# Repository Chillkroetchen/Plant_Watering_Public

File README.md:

# Plant_Watering
For use:
    1. configure variables in userConfig_sample.h
    2. rename userConfig_sample.h to userConfig.h
    3. build and upload to ESP32

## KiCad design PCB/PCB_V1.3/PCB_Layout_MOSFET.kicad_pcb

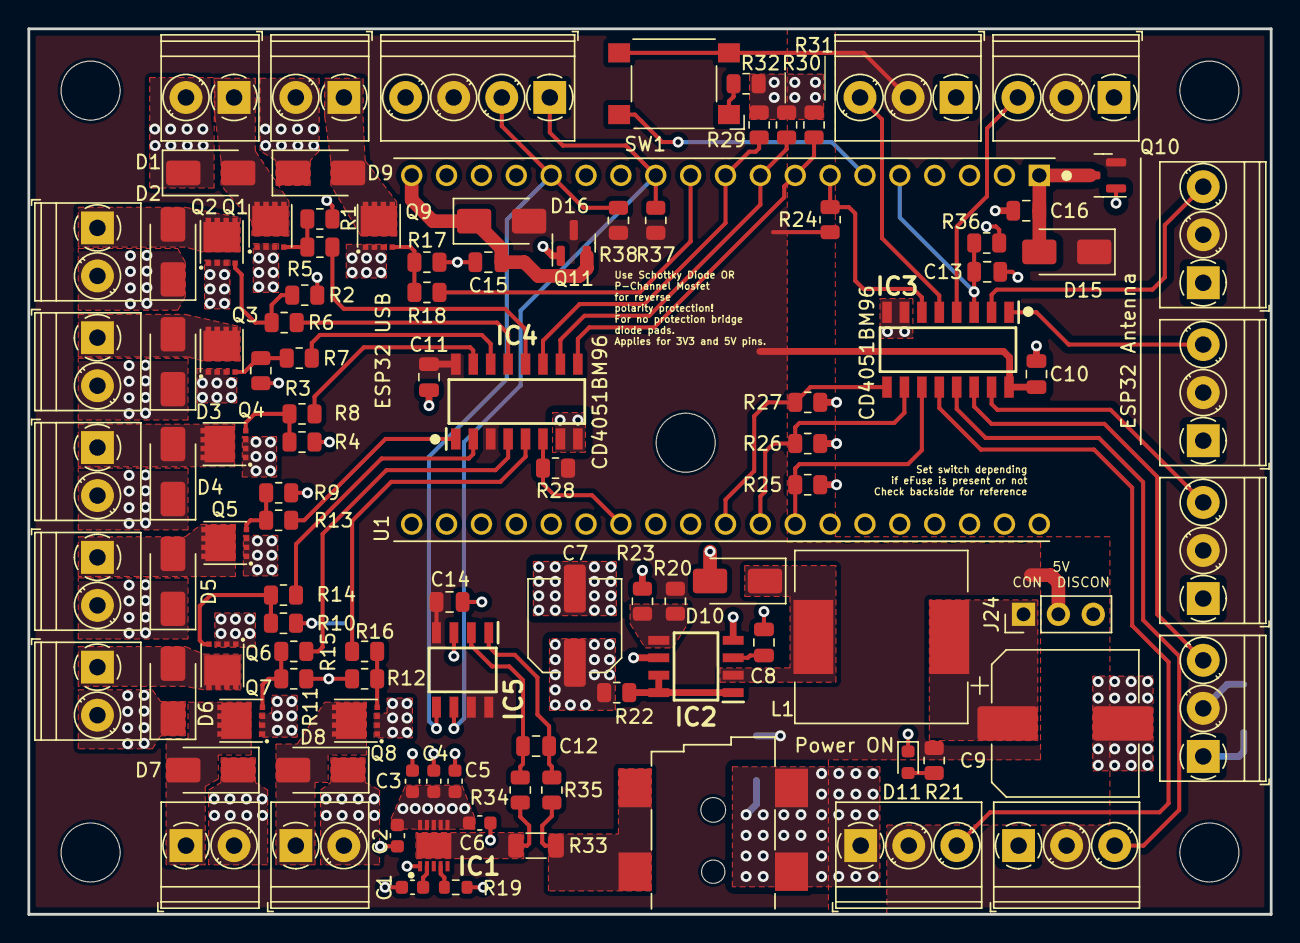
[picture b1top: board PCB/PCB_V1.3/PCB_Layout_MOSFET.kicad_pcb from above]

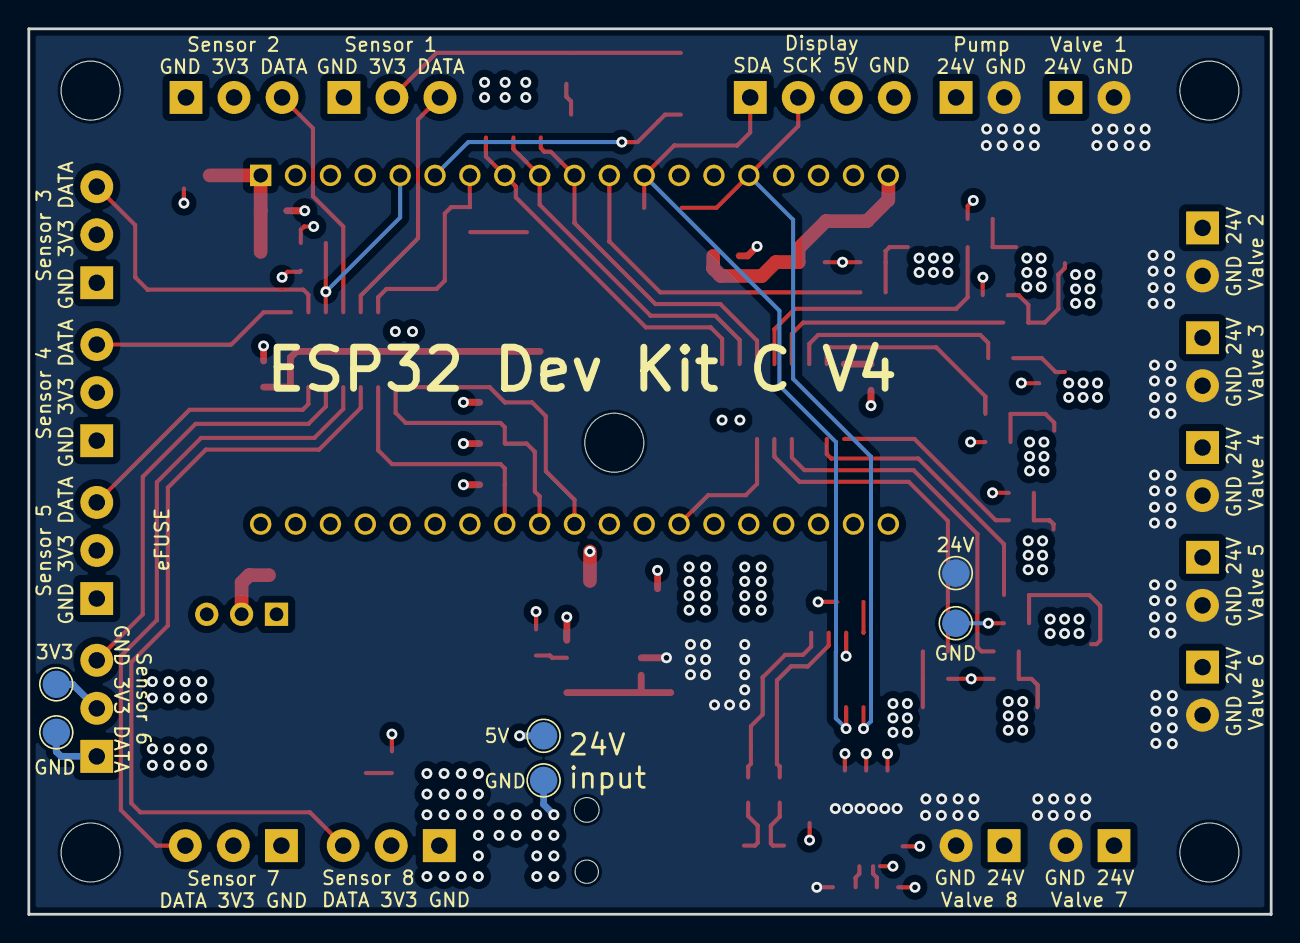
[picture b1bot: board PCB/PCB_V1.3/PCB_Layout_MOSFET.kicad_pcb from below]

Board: 4 copper layers, 90.5 x 64.5 mm, 117 parts (6 on the bottom side), 66 nets.

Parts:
C1: 470pF; C_0603_1608Metric
C2, C3, C4, C5, C6: 100nF; C_0603_1608Metric
C7: 100uF; CP_Elec_6.3x7.7
C8: 470pF; C_0805_2012Metric
C9: 470uF; CP_Elec_10x10.5
C10, C11, C12, C13, C14, C15, C16: 100nF; C_0805_2012Metric
D1, D2, D3, D4, D5, D6, D7, D8, D9, D10, D15, D16: 1N5819; D_SMA
D11: LED Blue; LED_0603_1608Metric
H1, H2, H3, H4, H5: MountingHole; MountingHole_4.3mm_M4
IC1: NIS4461MT3TXG; SON50P300X300X80-11N
IC2: MC34063ADR2G; SOIC127P600X175-8N
IC3, IC4: CD4051BM96; SOIC127P600X175-16N
IC5: INA219AIDR; SOIC127P600X175-8N
J1, J2, J3, J4, J5, J6, J7, J8, J9: Screw_Terminal_01x02; TerminalBlock_Phoenix_PT-1,5-2-3.5-H_1x02_P3.50mm_Horizontal
J10: KH-DC-050-2.0STM; CUI_PJ-002BH-SMT-TR
J11, J12, J13, J14, J15, J16, J17, J18: Screw_Terminal_01x03; TerminalBlock_Phoenix_PT-1,5-3-3.5-H_1x03_P3.50mm_Horizontal
J19: Screw_Terminal_01x04; TerminalBlock_Phoenix_PT-1,5-4-3.5-H_1x04_P3.50mm_Horizontal
J24: Conn_01x03; PinHeader_1x03_P2.54mm_Vertical
L1: 220uH; L_12x12mm_H8mm_3D
Q1, Q2, Q3, Q4, Q5, Q6, Q7, Q8, Q9: TPN2R805PL,L1Q; TPN2R805PLL1Q
Q10, Q11: SE3415; SOT-23
R1, R2, R3, R4, R9, R10, R11, R12, R17, R20, R37, R38: 3.6k; R_0805_2012Metric
R5, R6, R7, R8, R13, R14, R15, R16, R18: 330; R_0805_2012Metric
R19: 20; R_0603_1608Metric
R21, R23: 1.2k; R_0805_2012Metric
R22: 0.33; R_0805_2012Metric
R24, R25, R26, R27, R28, R29, R30, R31, R32, R36: 1M; R_0805_2012Metric
R33: R_Shunt_20m; R_1206_3216Metric
R34, R35: 0; R_0805_2012Metric
SW1: SW_MEC_5E; SW_SPST_Omron_B3FS-100xP_3D
TP1, TP2, TP3, TP4, TP5, TP6: TestPoint; TestPoint_Pad_D2.0mm
U1: ESP32-DEVKITC-32D; MODULE_ESP32-DEVKITC-32D

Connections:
3V3: D15.1 (K), J11.2, J12.2, J13.2, J14.2, J15.2, J16.2, J17.2, J18.2, Q10.2 (S), SW1.3 (K), SW1.4 (A), TP4.1
5V: C10.1, C11.1, C14.1, D16.2 (A), IC3.16 (VDD), IC4.3 (Z), IC4.16 (VDD), IC5.4 (VS), IC5.7 (A0), IC5.8 (A1), J19.3, J24.2, Q11.3 (D), R20.2, R21.2, R24.1, R28.1, R37.1, R38.1, TP1.1
5V_raw: C9.1, J24.1, L1.1
24V: C2.1, C3.1, C4.1, C5.1, C6.1, C7.1, D1.1 (K), D2.1 (K), D3.1 (K), D4.1 (K), D5.1 (K), D6.1 (K), D7.1 (K), D8.1 (K), D9.1 (K), IC1.6 (SRC_1), IC1.7 (SRC_2), IC1.8 (SRC_3), IC1.9 (SRC_4), IC1.10 (SRC_5), IC2.6 (VCC), J1.2, J2.2, J3.2, J4.2, J5.2, J6.2, J7.2, J8.2, J9.2, R19.1, R22.1, TP3.1
24V_raw: J10.1A, J10.1B, R33.1, R33.2, R35.2
24V_sensed: IC1.11 (EP), R33.3, R33.4, R34.2
/EXT_3V3: C16.1, D15.2 (A), Q10.3 (D), U1.1 (3V3)
/EXT_5V: C15.1, D16.1 (K), Q11.2 (S), U1.19 (EXT_5V)
/High Power Externals/Q1_drain: D1.2 (A), J1.1, Q1.5 (D_1), Q1.6 (D_2), Q1.7 (D_3), Q1.8 (D_4), Q1.9 (D_5)
/High Power Externals/Q1_gate: Q1.4 (G), R1.1, R5.1
/High Power Externals/Q2_drain: D2.2 (A), J2.1, Q2.5 (D_1), Q2.6 (D_2), Q2.7 (D_3), Q2.8 (D_4), Q2.9 (D_5)
/High Power Externals/Q2_gate: Q2.4 (G), R2.1, R6.1
/High Power Externals/Q3_drain: D3.2 (A), J3.1, Q3.5 (D_1), Q3.6 (D_2), Q3.7 (D_3), Q3.8 (D_4), Q3.9 (D_5)
/High Power Externals/Q3_gate: Q3.4 (G), R3.1, R7.1
/High Power Externals/Q4_drain: D4.2 (A), J4.1, Q4.5 (D_1), Q4.6 (D_2), Q4.7 (D_3), Q4.8 (D_4), Q4.9 (D_5)
/High Power Externals/Q4_gate: Q4.4 (G), R4.1, R8.1
/High Power Externals/Q5_drain: D5.2 (A), J5.1, Q5.5 (D_1), Q5.6 (D_2), Q5.7 (D_3), Q5.8 (D_4), Q5.9 (D_5)
/High Power Externals/Q5_gate: Q5.4 (G), R9.1, R13.1
/High Power Externals/Q6_drain: D6.2 (A), J6.1, Q6.5 (D_1), Q6.6 (D_2), Q6.7 (D_3), Q6.8 (D_4), Q6.9 (D_5)
/High Power Externals/Q6_gate: Q6.4 (G), R10.1, R14.1
/High Power Externals/Q7_drain: D7.2 (A), J7.1, Q7.5 (D_1), Q7.6 (D_2), Q7.7 (D_3), Q7.8 (D_4), Q7.9 (D_5)
/High Power Externals/Q7_gate: Q7.4 (G), R11.1, R15.1
/High Power Externals/Q8_drain: D8.2 (A), J8.1, Q8.5 (D_1), Q8.6 (D_2), Q8.7 (D_3), Q8.8 (D_4), Q8.9 (D_5)
/High Power Externals/Q8_gate: Q8.4 (G), R12.1, R16.1
/High Power Externals/Q9_drain: D9.2 (A), J9.1, Q9.5 (D_1), Q9.6 (D_2), Q9.7 (D_3), Q9.8 (D_4), Q9.9 (D_5)
/High Power Externals/Q9_gate: Q9.4 (G), R17.1, R18.1
/Power Supply/CII: IC2.5 (CII), R20.1, R23.2
/Power Supply/I Lim: IC1.4 (ILIM), R19.2
/Power Supply/LED: D11.2 (A), R21.1
/Power Supply/SWC: IC2.1 (SWC), IC2.7 (IPK), IC2.8 (DRC), R22.2
/Power Supply/SWE: D10.1 (K), IC2.2 (SWE), L1.2
/Power Supply/TC: C8.1, IC2.3 (TC)
/Power Supply/dV/dT: C1.1, IC1.2 (DV/DT)
Button: SW1.2, U1.6 (IO35)
GND: C1.2, C2.2, C3.2, C4.2, C5.2, C6.2, C7.2, C8.2, C9.2, C10.2, C11.2, C13.2, C14.2, C15.2, C16.2, D10.2 (A), D11.1 (K), IC1.1 (GND), IC2.4 (GND), IC3.7 (VEE), IC3.8 (VSS), IC4.7 (VEE), IC4.8 (VSS), IC5.3 (GND), J10.2, J10.3, J11.1, J12.1, J13.1, J14.1, J15.1, J16.1, J17.1, J18.1, J19.4, Q1.1 (S_1), Q1.2 (S_2), Q1.3 (S_3), Q2.1 (S_1), Q2.2 (S_2), Q2.3 (S_3), Q3.1 (S_1), Q3.2 (S_2), Q3.3 (S_3), Q4.1 (S_1), Q4.2 (S_2), Q4.3 (S_3), Q5.1 (S_1), Q5.2 (S_2), Q5.3 (S_3), Q6.1 (S_1), Q6.2 (S_2), Q6.3 (S_3), Q7.1 (S_1), Q7.2 (S_2), Q7.3 (S_3), Q8.1 (S_1), Q8.2 (S_2), Q8.3 (S_3), Q9.1 (S_1), Q9.2 (S_2), Q9.3 (S_3), Q10.1 (G), Q11.1 (G), R1.2, R2.2, R3.2, R4.2, R9.2, R10.2, R11.2, R12.2, R17.2, R23.1, R25.1, R26.1, R27.1, R29.1, R30.1, R31.1, R32.2, R36.1, TP2.1, TP5.1, TP6.1, U1.14 (GND1), U1.20 (GND3), U1.26 (GND2)
unnamed: C12.1, IC5.1 (IN+), R35.1
unnamed: C12.2, IC5.2 (IN-), R34.1
unnamed: R32.1, SW1.1
Pump_Gate: R18.2, U1.11 (IO27)
SCL: IC5.5 (SCL), J19.2, R38.2, U1.15 (IO13)
SDA: IC5.6 (SDA), J19.1, R37.2, U1.12 (IO14)
Sensors_Enable: IC3.6 (~E), R24.2, U1.7 (IO32)
Sensors_Select1: IC3.11 (S1), R25.2, U1.27 (IO19)
Sensors_Select2: IC3.10 (S2), R26.2, U1.28 (IO18)
Sensors_Select3: IC3.9 (S3), R27.2, U1.29 (IO5)
Sensors_Signal: C13.1, IC3.3 (Z), R36.2, U1.5 (IO34)
Valves_Enable: IC4.6 (~E), R28.2, U1.32 (IO4)
Valves_Select1: IC4.11 (S1), R29.2, U1.10 (IO26)
Valves_Select2: IC4.10 (S2), R30.2, U1.9 (IO25)
Valves_Select3: IC4.9 (S3), R31.2, U1.8 (IO33)
Y0: IC4.13 (Y0), R6.2
Y0.2: IC3.13 (Y0), J17.3
Y1: IC4.14 (Y1), R7.2
Y1.2: IC3.14 (Y1), J16.3
Y2: IC4.15 (Y2), R8.2
Y2.2: IC3.15 (Y2), J15.3
Y3: IC4.12 (Y3), R5.2
Y3.2: IC3.12 (Y3), J18.3
Y4: IC4.1 (Y4), R13.2
Y4.2: IC3.1 (Y4), J14.3
Y5: IC4.5 (Y5), R16.2
Y5.2: IC3.5 (Y5), J11.3
Y6: IC4.2 (Y6), R14.2
Y6.2: IC3.2 (Y6), J13.3
Y7: IC4.4 (Y7), R15.2
Y7.2: IC3.4 (Y7), J12.3

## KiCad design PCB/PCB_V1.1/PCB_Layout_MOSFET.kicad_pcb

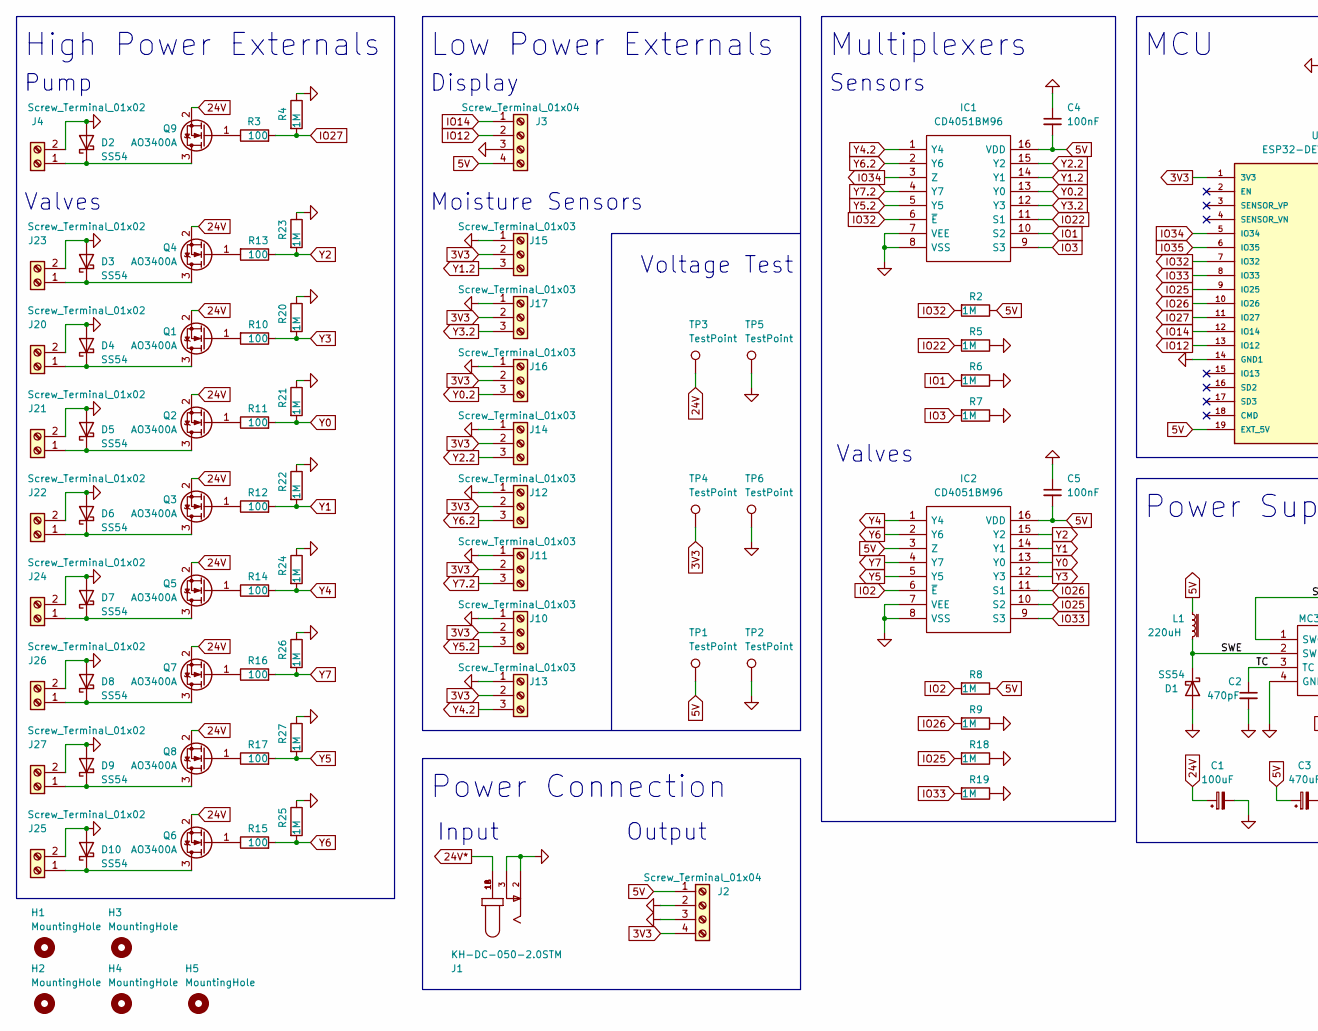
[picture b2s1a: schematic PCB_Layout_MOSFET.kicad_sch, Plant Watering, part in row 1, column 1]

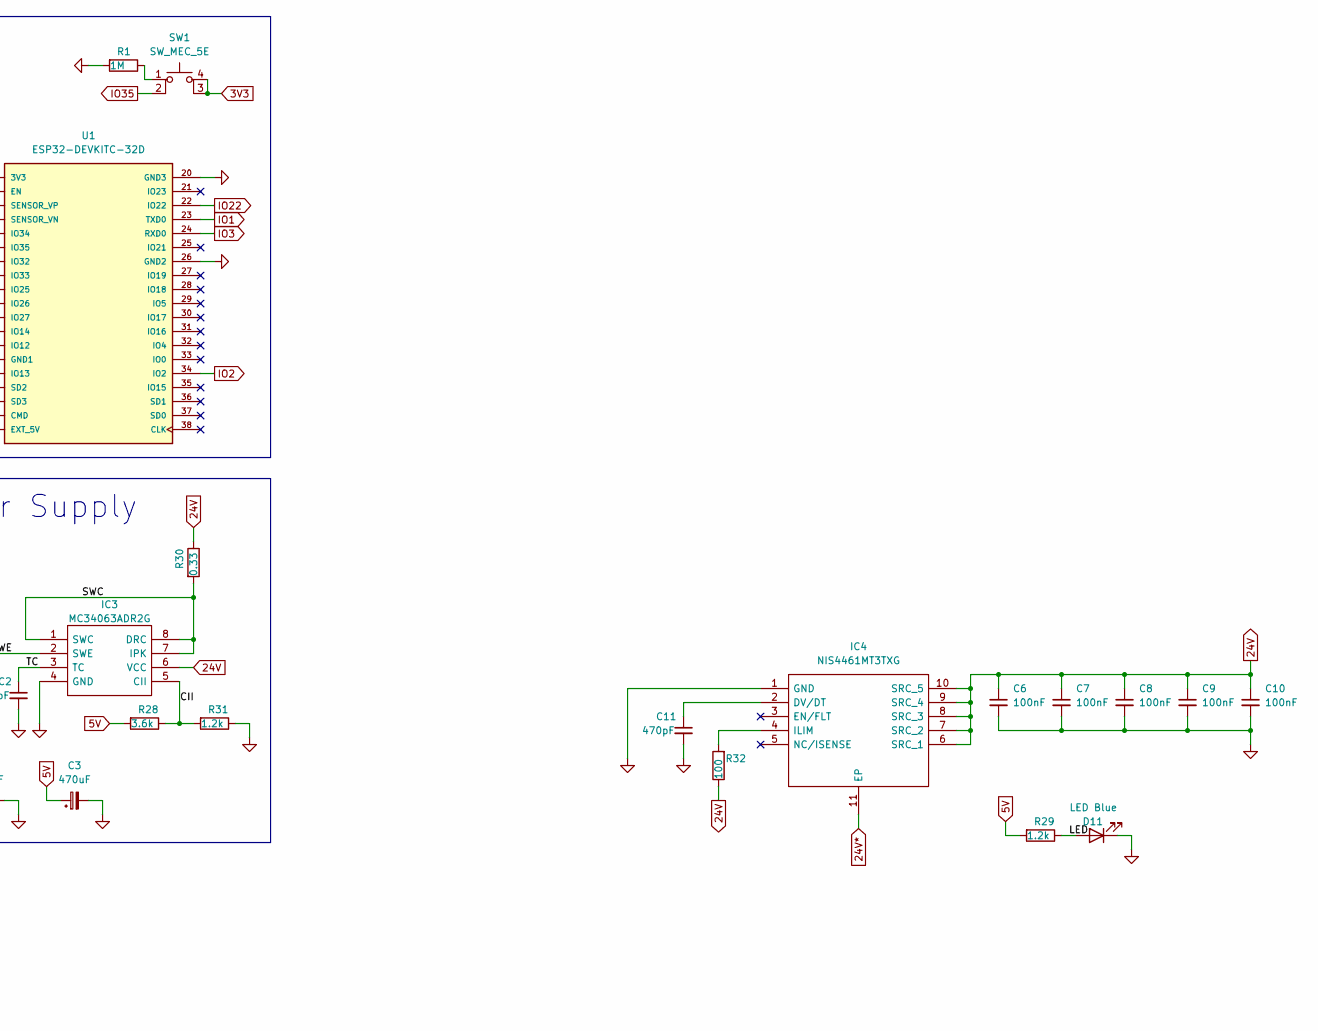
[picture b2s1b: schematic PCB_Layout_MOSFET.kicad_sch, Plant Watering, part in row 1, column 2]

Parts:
C1: 100uF; CP_Elec_6.3x7.7; LCSC C3001220
C2: 470pF; C_0805_2012Metric; LCSC C1743
C3: 470uF; CP_Elec_10x10.5; LCSC C129479
C4, C5: 100nF; C_0805_2012Metric; LCSC C49678
C6, C7, C8, C9, C10: 100nF; C_0603_1608Metric; LCSC C14663
C11: 470pF; C_0603_1608Metric; LCSC C1620
D1, D2, D3, D4, D5, D6, D7, D8, D9, D10: SS54; D_SMA; LCSC C22452
D11: LED Blue; LED_0603_1608Metric; LCSC C72041
H1, H2, H3, H4, H5: MountingHole; MountingHole_4.3mm_M4
IC1, IC2: CD4051BM96; SOIC127P600X175-16N; Manufacturer_Part_Number CD4051BM96; LCSC C21379
IC3: MC34063ADR2G; SOIC127P600X175-8N; LCSC C32078
IC4: NIS4461MT3TXG; SON50P300X300X80-11N; Mouser Part Number 863-NIS4461MT3TXG
J1: KH-DC-050-2.0STM; CUI_PJ-002BH-SMT-TR; LCSC C2847201
J2, J3: Screw_Terminal_01x04; TerminalBlock_Phoenix_PT-1,5-4-3.5-H_1x04_P3.50mm_Horizontal; LCSC C2757925
J4, J20, J21, J22, J23, J24, J25, J26, J27: Screw_Terminal_01x02; TerminalBlock_Phoenix_PT-1,5-2-3.5-H_1x02_P3.50mm_Horizontal; LCSC C474930
J10, J11, J12, J13, J14, J15, J16, J17: Screw_Terminal_01x03; TerminalBlock_Phoenix_PT-1,5-3-3.5-H_1x03_P3.50mm_Horizontal; LCSC C474931
L1: 220uH; L_1210_3225Metric; LCSC C394104
Q1, Q2, Q3, Q4, Q5, Q6, Q7, Q8, Q9: AO3400A; SOT-23; LCSC C20917
R1, R2, R4, R5, R6, R7, R8, R9, R18, R19, R20, R21, R22, R23, R24, R25, R26, R27: 1M; R_0805_2012Metric; LCSC C17514
R3, R10, R11, R12, R13, R14, R15, R16, R17: 100; R_0805_2012Metric; LCSC C17408
R28: 3.6k; R_0805_2012Metric; LCSC C18359
R29, R31: 1.2k; R_0805_2012Metric; LCSC C17379
R30: 0.33; R_0805_2012Metric; LCSC C491232
R32: 100; R_0603_1608Metric; LCSC C22775
SW1: SW_MEC_5E; SW_SPST_Omron_B3FS-100xP_3D; LCSC C231324
TP1, TP2, TP3, TP4, TP5, TP6: TestPoint; TestPoint_Pad_D2.0mm
U1: ESP32-DEVKITC-32D; MODULE_ESP32-DEVKITC-32D; PARTREV 4

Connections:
3V3: J2.4, J10.2, J11.2, J12.2, J13.2, J14.2, J15.2, J16.2, J17.2, SW1.3 (K), SW1.4 (A), TP4.1, U1.1 (3V3)
5V: C3.1, C4.2, C5.2, IC1.16 (VDD), IC2.3 (Z), IC2.16 (VDD), J2.1, J3.4, L1.1, R2.1, R8.1, R28.2, R29.2, TP1.1, U1.19 (EXT_5V)
24V: C1.1, C6.1, C7.1, C8.1, C9.1, C10.1, IC3.6 (VCC), IC4.6 (SRC_1), IC4.7 (SRC_2), IC4.8 (SRC_3), IC4.9 (SRC_4), IC4.10 (SRC_5), Q1.2 (S), Q2.2 (S), Q3.2 (S), Q4.2 (S), Q5.2 (S), Q6.2 (S), Q7.2 (S), Q8.2 (S), Q9.2 (S), R30.1, R32.1, TP3.1
24V*: IC4.11 (EP), J1.1A, J1.1B
/CII: IC3.5 (CII), R28.1, R31.2
/LED: D11.2 (A), R29.1
/SWC: IC3.1 (SWC), IC3.7 (IPK), IC3.8 (DRC), R30.2
/SWE: D1.1 (K), IC3.2 (SWE), L1.2
/TC: C2.1, IC3.3 (TC)
GND: C1.2, C2.2, C3.2, C4.1, C5.1, C6.2, C7.2, C8.2, C9.2, C10.2, C11.2, D1.2 (A), D2.2 (A), D3.2 (A), D4.2 (A), D5.2 (A), D6.2 (A), D7.2 (A), D8.2 (A), D9.2 (A), D10.2 (A), D11.1 (K), IC1.7 (VEE), IC1.8 (VSS), IC2.7 (VEE), IC2.8 (VSS), IC3.4 (GND), IC4.1 (GND), J1.2, J1.3, J2.2, J2.3, J3.3, J4.2, J10.1, J11.1, J12.1, J13.1, J14.1, J15.1, J16.1, J17.1, J20.2, J21.2, J22.2, J23.2, J24.2, J25.2, J26.2, J27.2, R1.2, R4.1, R5.1, R6.1, R7.1, R9.1, R18.1, R19.1, R20.1, R21.1, R22.1, R23.1, R24.1, R25.1, R26.1, R27.1, R31.1, TP2.1, TP5.1, TP6.1, U1.14 (GND1), U1.20 (GND3), U1.26 (GND2)
IO1: IC1.10 (S2), R6.2, U1.23 (TXD0)
IO2: IC2.6 (~E), R8.2, U1.34 (IO2)
IO3: IC1.9 (S3), R7.2, U1.24 (RXD0)
IO12: J3.2, U1.13 (IO12)
IO14: J3.1, U1.12 (IO14)
IO22: IC1.11 (S1), R5.2, U1.22 (IO22)
IO25: IC2.10 (S2), R18.2, U1.9 (IO25)
IO26: IC2.11 (S1), R9.2, U1.10 (IO26)
IO27: R3.2, R4.2, U1.11 (IO27)
IO32: IC1.6 (~E), R2.2, U1.7 (IO32)
IO33: IC2.9 (S3), R19.2, U1.8 (IO33)
IO34: IC1.3 (Z), U1.5 (IO34)
IO35: SW1.2, U1.6 (IO35)
unnamed: C11.1, IC4.2 (DV/DT)
unnamed: D2.1 (K), J4.1, Q9.3 (D)
unnamed: D3.1 (K), J23.1, Q4.3 (D)
unnamed: D4.1 (K), J20.1, Q1.3 (D)
unnamed: D5.1 (K), J21.1, Q2.3 (D)
unnamed: D6.1 (K), J22.1, Q3.3 (D)
unnamed: D7.1 (K), J24.1, Q5.3 (D)
unnamed: D8.1 (K), J26.1, Q7.3 (D)
unnamed: D9.1 (K), J27.1, Q8.3 (D)
unnamed: D10.1 (K), J25.1, Q6.3 (D)
unnamed: IC4.4 (ILIM), R32.2
unnamed: Q1.1 (G), R10.2
unnamed: Q2.1 (G), R11.1
unnamed: Q3.1 (G), R12.1
unnamed: Q4.1 (G), R13.2
unnamed: Q5.1 (G), R14.1
unnamed: Q6.1 (G), R15.1
unnamed: Q7.1 (G), R16.1
unnamed: Q8.1 (G), R17.1
unnamed: Q9.1 (G), R3.1
unnamed: R1.1, SW1.1
Y0: IC2.13 (Y0), R11.2, R21.2
Y0.2: IC1.13 (Y0), J16.3
Y1: IC2.14 (Y1), R12.2, R22.2
Y1.2: IC1.14 (Y1), J15.3
Y2: IC2.15 (Y2), R13.1, R23.2
Y2.2: IC1.15 (Y2), J14.3
Y3: IC2.12 (Y3), R10.1, R20.2
Y3.2: IC1.12 (Y3), J17.3
Y4: IC2.1 (Y4), R14.2, R24.2
Y4.2: IC1.1 (Y4), J13.3
Y5: IC2.5 (Y5), R17.2, R27.2
Y5.2: IC1.5 (Y5), J10.3
Y6: IC2.2 (Y6), R15.2, R25.2
Y6.2: IC1.2 (Y6), J12.3
Y7: IC2.4 (Y7), R16.2, R26.2
Y7.2: IC1.4 (Y7), J11.3

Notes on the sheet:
Power Supply
Valves
Multiplexers
Pump
Input
Moisture Sensors
Sensors
Power Connection
Output
Low Power Externals
Voltage Test
MCU
High Power Externals
Display

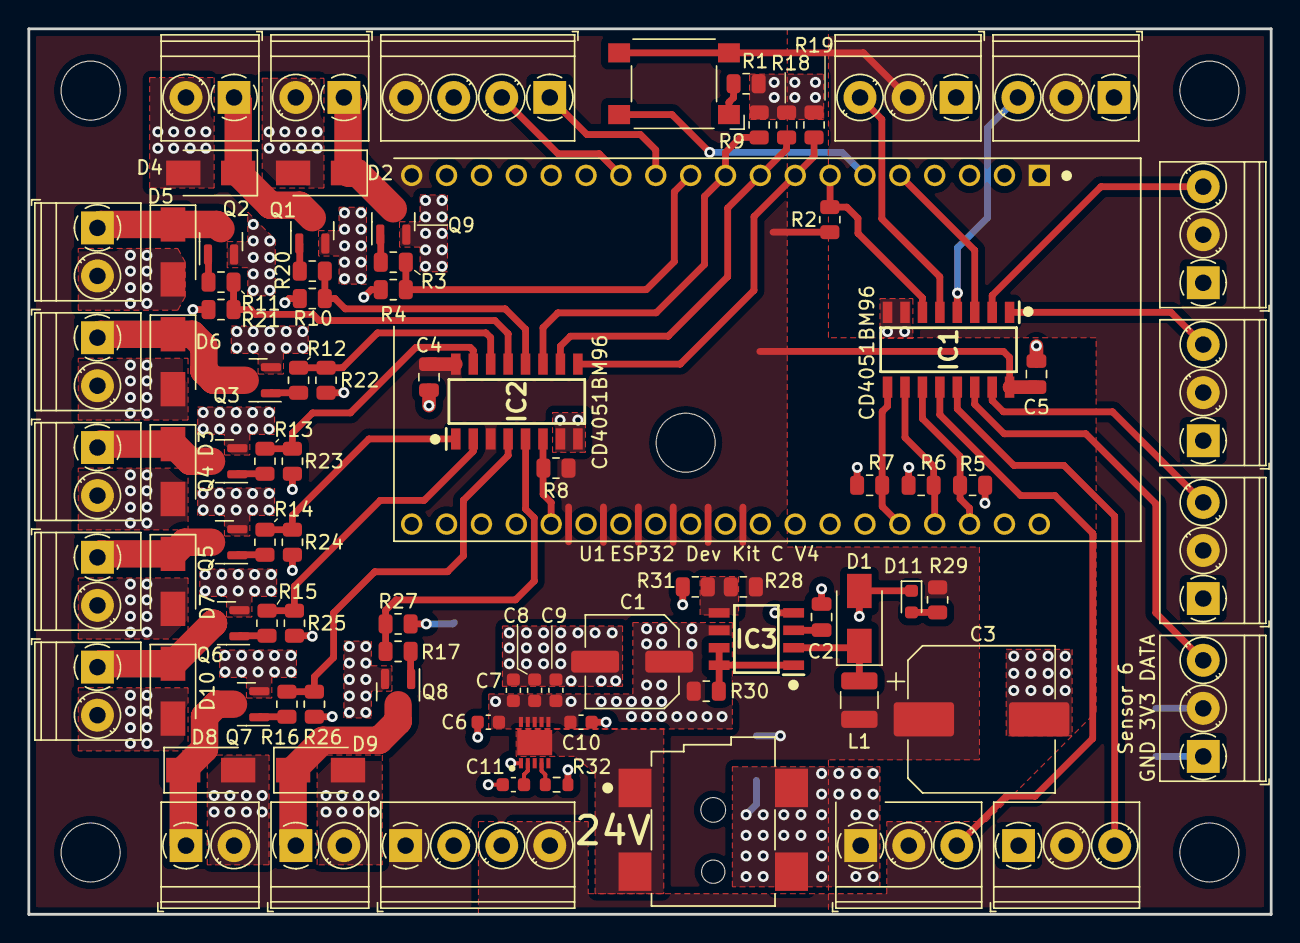
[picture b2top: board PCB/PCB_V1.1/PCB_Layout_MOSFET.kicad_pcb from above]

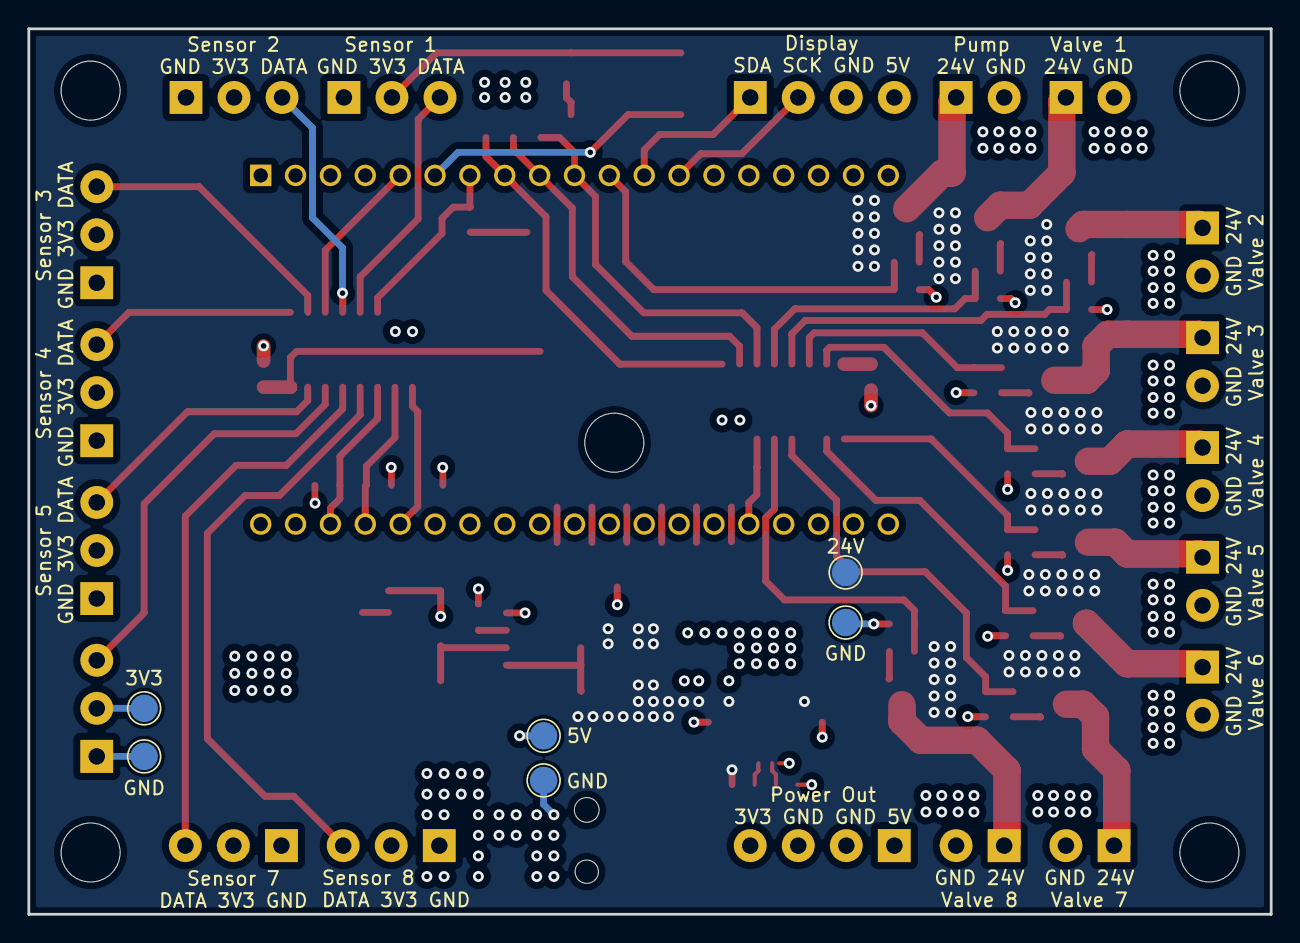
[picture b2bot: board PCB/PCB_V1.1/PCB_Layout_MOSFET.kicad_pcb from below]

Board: 4 copper layers, 90.5 x 64.5 mm, 101 parts (6 on the bottom side), 60 nets.

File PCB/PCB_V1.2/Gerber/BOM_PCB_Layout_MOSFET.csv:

Comment,Designator,Footprint,LCSC
"470pF","C1","Capacitor_SMD:C_0805_2012Metric","C1743"
"470uF","C2","Capacitor_SMD:CP_Elec_10x10.5","C129479"
"100uF","C3","Capacitor_SMD:CP_Elec_6.3x7.7","C3001220"
"LED Blue","D1","LED_SMD:LED_0603_1608Metric","C72041"
"SS54","D2,D3,D4,D5,D6,D7,D8,D9,D10,D11","Diode_SMD:D_SMA","C22452"
"HEF4051BT,653","IC1,IC2","SamacSys_Parts:SOIC127P600X175-16N","C11351"
"MC34063ADR2G","IC3","SamacSys_Parts:SOIC127P600X175-8N","C32078"
"KH-DC-050-2.0STM","J1","PersonalLibrary:CUI_PJ-002BH-SMT-TR","C2847201"
"Screw_Terminal_01x03","J10,J11,J12,J13,J14,J15,J16,J17","TerminalBlock_Phoenix:TerminalBlock_Phoenix_PT-1,5-3-3.5-H_1x03_P3.50mm_Horizontal","C474931"
"Screw_Terminal_01x04","J2,J3","TerminalBlock_Phoenix:TerminalBlock_Phoenix_PT-1,5-4-3.5-H_1x04_P3.50mm_Horizontal","C2757925"
"Screw_Terminal_01x02","J4,J20,J21,J22,J23,J24,J25,J26,J27","TerminalBlock_Phoenix:TerminalBlock_Phoenix_PT-1,5-2-3.5-H_1x02_P3.50mm_Horizontal","C474930"
"220uH","L1","Inductor_SMD:L_1210_3225Metric","C394104"
"AO3400A","Q1,Q2,Q3,Q4,Q5,Q6,Q7,Q8,Q9","Package_TO_SOT_SMD:SOT-23","C20917"
"1M","R1,R4,R20,R21,R22,R23,R24,R25,R26,R27","Resistor_SMD:R_0805_2012Metric","C17514"
"100","R2,R3,R10,R11,R12,R13,R14,R15,R16,R17","Resistor_SMD:R_0805_2012Metric","C17408"
"3.6k","R5","Resistor_SMD:R_0805_2012Metric","C18359"
"0.33","R6","Resistor_SMD:R_0805_2012Metric","C491232"
"1.2k","R7","Resistor_SMD:R_0805_2012Metric","C17379"
"SW_MEC_5E","SW1","PersonalLibrary:SW_SPST_Omron_B3FS-100xP_3D","C231324"

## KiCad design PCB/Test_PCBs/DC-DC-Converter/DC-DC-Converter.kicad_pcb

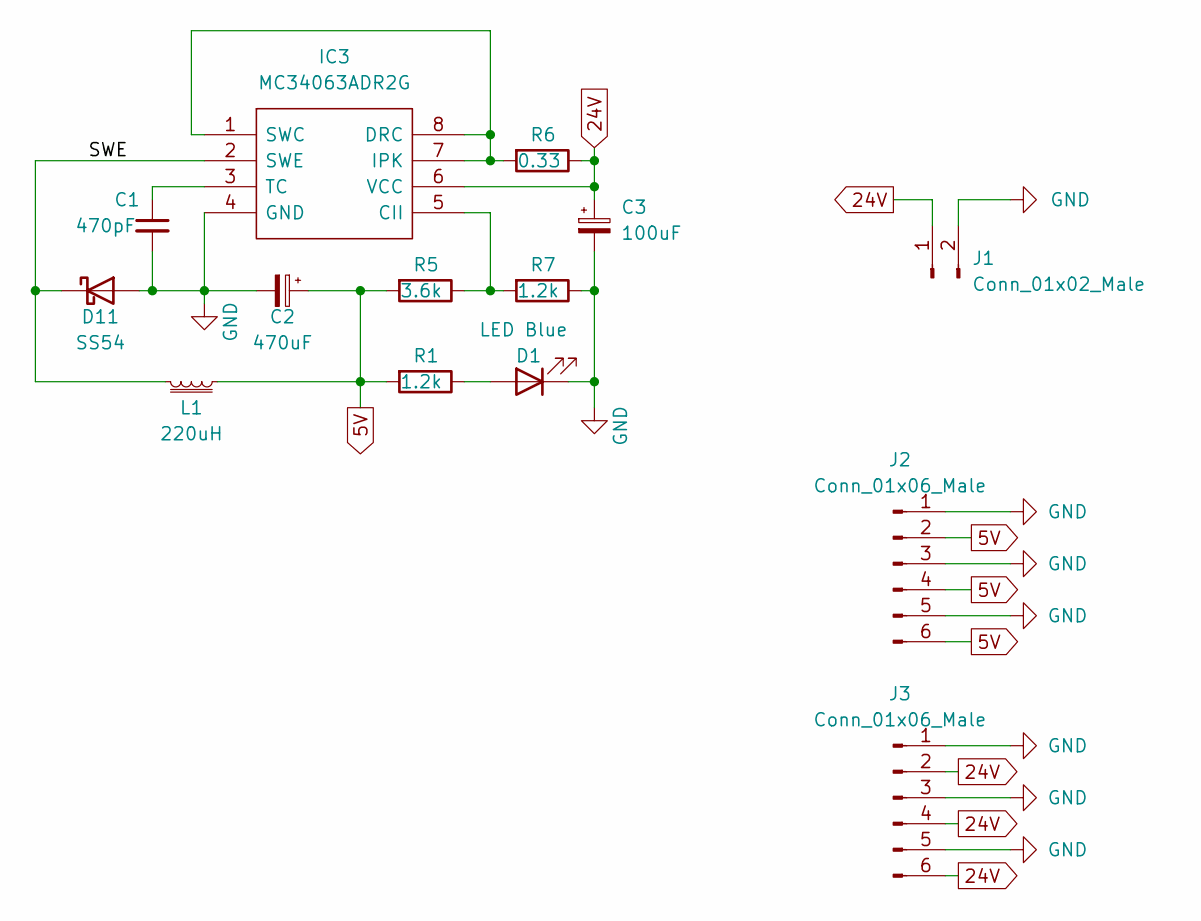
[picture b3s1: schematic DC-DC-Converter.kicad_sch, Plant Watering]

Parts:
C1: 470pF; C_0805_2012Metric; LCSC C1743
C2: 470uF; CP_Elec_10x10.5; LCSC C129479
C3: 100uF; CP_Elec_6.3x7.7; LCSC C3001220
D1: LED Blue; LED_0603_1608Metric; LCSC C72041
D11: SS54; D_SMA; LCSC C22452
IC3: MC34063ADR2G; SOIC127P600X175-8N; LCSC C32078
J1: Conn_01x02_Male; PinHeader_1x02_P2.54mm_Vertical
J2, J3: Conn_01x06_Male; PinHeader_2x03_P2.54mm_Vertical
L1: 220uH; L_1210_3225Metric; LCSC C394104
R1, R7: 1.2k; R_0805_2012Metric; LCSC C17379
R5: 3.6k; R_0805_2012Metric; LCSC C18359
R6: 0.33; R_0805_2012Metric; LCSC C491232

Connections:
5V: C2.1, J2.2, J2.4, J2.6, L1.1, R1.2, R5.2
24V: C3.1, IC3.6 (VCC), J1.1, J3.2, J3.4, J3.6, R6.1
/SWE: D11.1 (K), IC3.2 (SWE), L1.2
GND: C1.2, C2.2, C3.2, D1.1 (K), D11.2 (A), IC3.4 (GND), J1.2, J2.1, J2.3, J2.5, J3.1, J3.3, J3.5, R7.1
unnamed: C1.1, IC3.3 (TC)
unnamed: D1.2 (A), R1.1
unnamed: IC3.1 (SWC), IC3.7 (IPK), IC3.8 (DRC), R6.2
unnamed: IC3.5 (CII), R5.1, R7.2

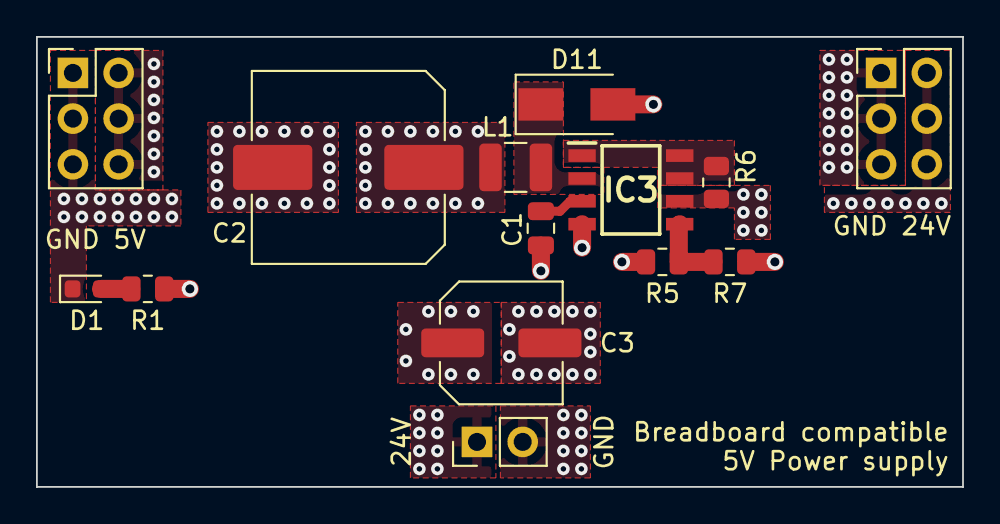
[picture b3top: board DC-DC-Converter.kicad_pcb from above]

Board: 4 copper layers, 51.5 x 25.0 mm, 14 parts (0 on the bottom side), 8 nets.

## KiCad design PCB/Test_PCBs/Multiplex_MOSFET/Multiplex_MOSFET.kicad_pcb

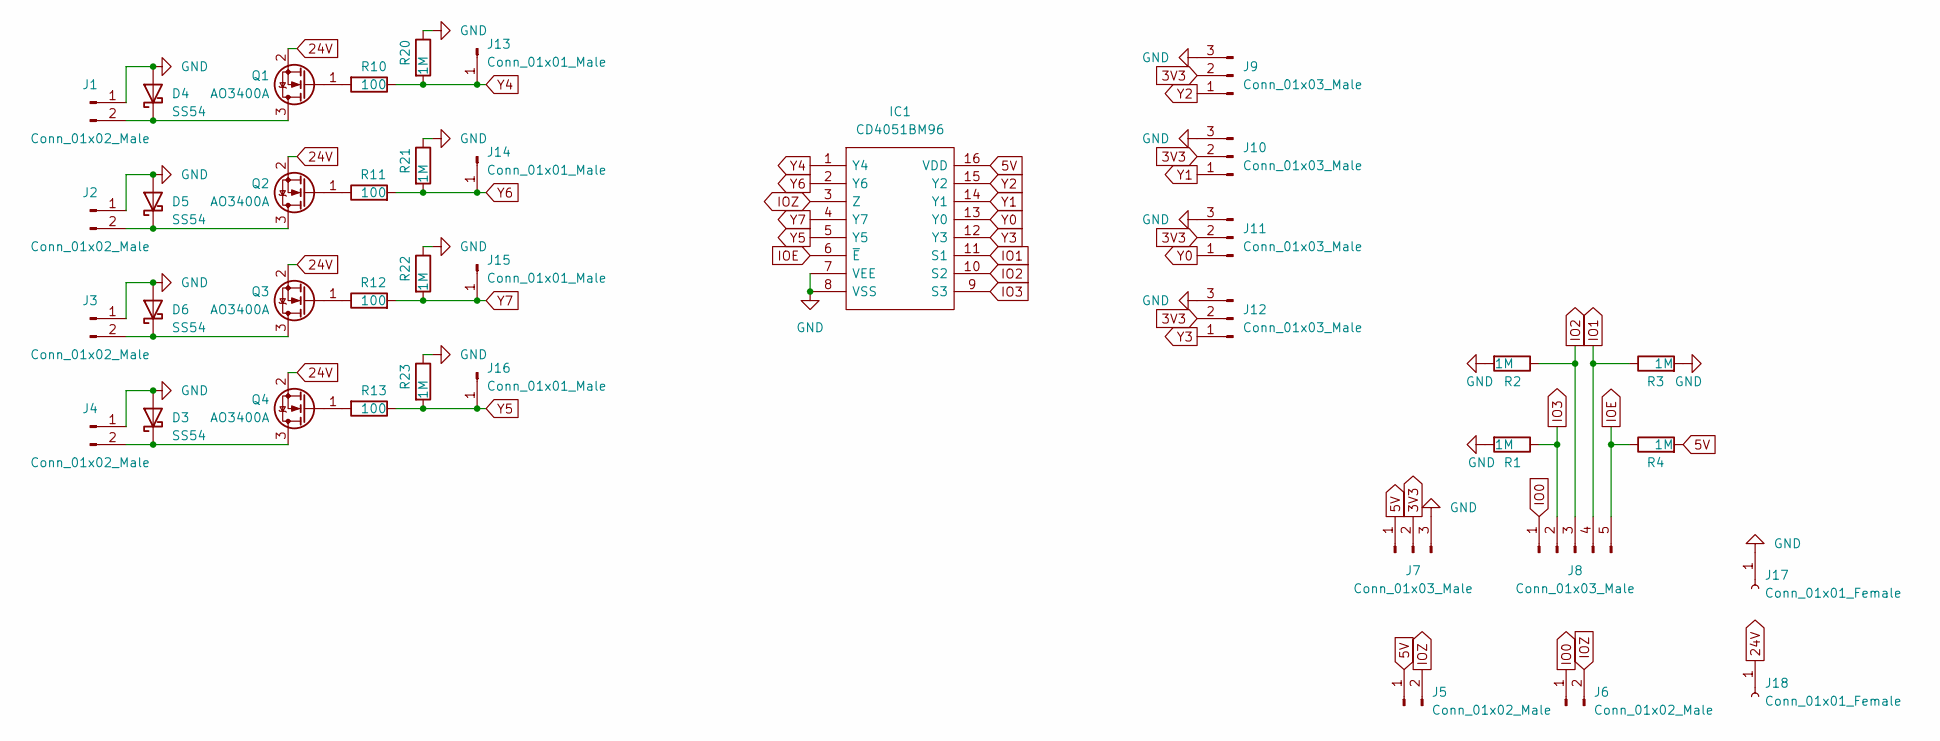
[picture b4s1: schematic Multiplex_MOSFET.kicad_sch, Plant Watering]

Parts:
D3, D4, D5, D6: SS54; D_SMA; LCSC C22452
IC1: CD4051BM96; SOIC127P600X175-16N; Manufacturer_Part_Number CD4051BM96; LCSC C21379
J1, J2, J3, J4, J5, J6: Conn_01x02_Male; PinHeader_1x02_P2.54mm_Vertical
J7, J9, J10, J11, J12: Conn_01x03_Male; PinHeader_1x03_P2.54mm_Vertical
J8: Conn_01x03_Male; PinHeader_1x05_P2.54mm_Vertical
J13, J14, J15, J16: Conn_01x01_Male; PinHeader_1x01_P2.54mm_Vertical
J17, J18: Conn_01x01_Female; MountingHole_2.2mm_M2_ISO14580_Pad
Q1, Q2, Q3, Q4: AO3400A; SOT-23; LCSC C20917
R1, R2, R3, R4, R20, R21, R22, R23: 1M; R_0805_2012Metric; LCSC C17514
R10, R11, R12, R13: 100; R_0805_2012Metric; LCSC C17408

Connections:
3V3: J7.2, J9.2, J10.2, J11.2, J12.2
5V: IC1.16 (VDD), J5.1, J7.1, R4.2
24V: J18.1, Q1.2 (S), Q2.2 (S), Q3.2 (S), Q4.2 (S)
GND: D3.2 (A), D4.2 (A), D5.2 (A), D6.2 (A), IC1.7 (VEE), IC1.8 (VSS), J1.1, J2.1, J3.1, J4.1, J7.3, J9.3, J10.3, J11.3, J12.3, J17.1, R1.2, R2.2, R3.2, R20.1, R21.1, R22.1, R23.1
IO0: J6.1, J8.1
IO1: IC1.11 (S1), J8.4, R3.1
IO2: IC1.10 (S2), J8.3, R2.1
IO3: IC1.9 (S3), J8.2, R1.1
IOE: IC1.6 (~E), J8.5, R4.1
IOZ: IC1.3 (Z), J5.2, J6.2
unnamed: D3.1 (K), J4.2, Q4.3 (D)
unnamed: D4.1 (K), J1.2, Q1.3 (D)
unnamed: D5.1 (K), J2.2, Q2.3 (D)
unnamed: D6.1 (K), J3.2, Q3.3 (D)
unnamed: Q1.1 (G), R10.2
unnamed: Q2.1 (G), R11.1
unnamed: Q3.1 (G), R12.1
unnamed: Q4.1 (G), R13.2
Y0: IC1.13 (Y0), J11.1
Y1: IC1.14 (Y1), J10.1
Y2: IC1.15 (Y2), J9.1
Y3: IC1.12 (Y3), J12.1
Y4: IC1.1 (Y4), J13.1, R10.1, R20.2
Y5: IC1.5 (Y5), J16.1, R13.1, R23.2
Y6: IC1.2 (Y6), J14.1, R11.2, R21.2
Y7: IC1.4 (Y7), J15.1, R12.2, R22.2

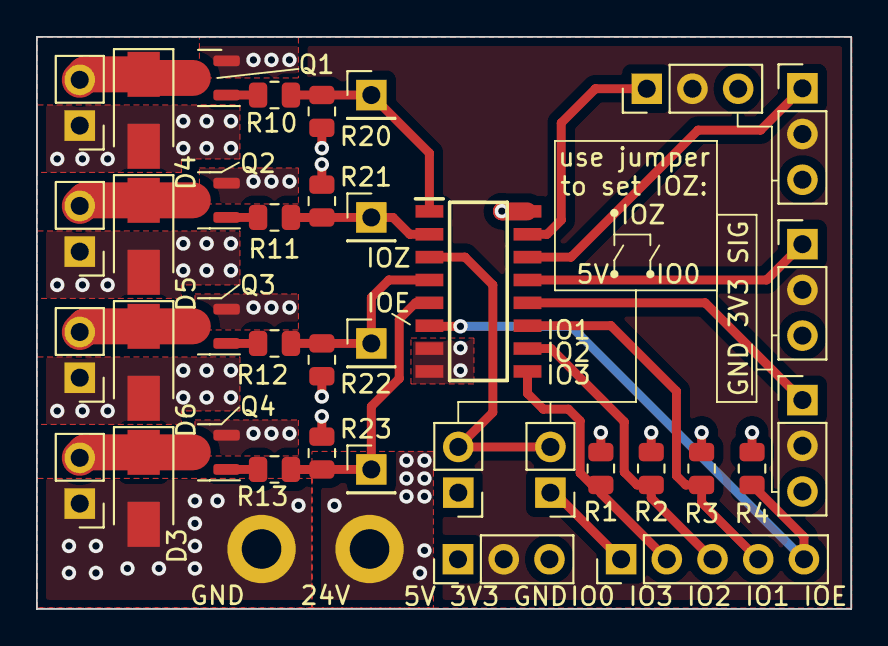
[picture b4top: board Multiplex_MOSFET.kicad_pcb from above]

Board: 4 copper layers, 45.2 x 31.8 mm, 39 parts (0 on the bottom side), 26 nets.

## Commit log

2023-01-16 Remove private info
2023-04-09 style: change gitignore refactor: introduce userConfig.h
2023-04-09 style: change .gitignore
2023-04-09 style: fixed .gitignore to really ignore .clang-format
2023-04-09 style: deleted .vscode directory from repository
2023-04-09 refactor: remove .clang-format from repository
2023-04-10 refactor: removed unused libraries
2023-04-10 refactor: moved sensible data from main.cpp to userconfig.h
2025-01-11 PCB: added power sensor
2025-01-11 feat: added library for INA260 power sensor
